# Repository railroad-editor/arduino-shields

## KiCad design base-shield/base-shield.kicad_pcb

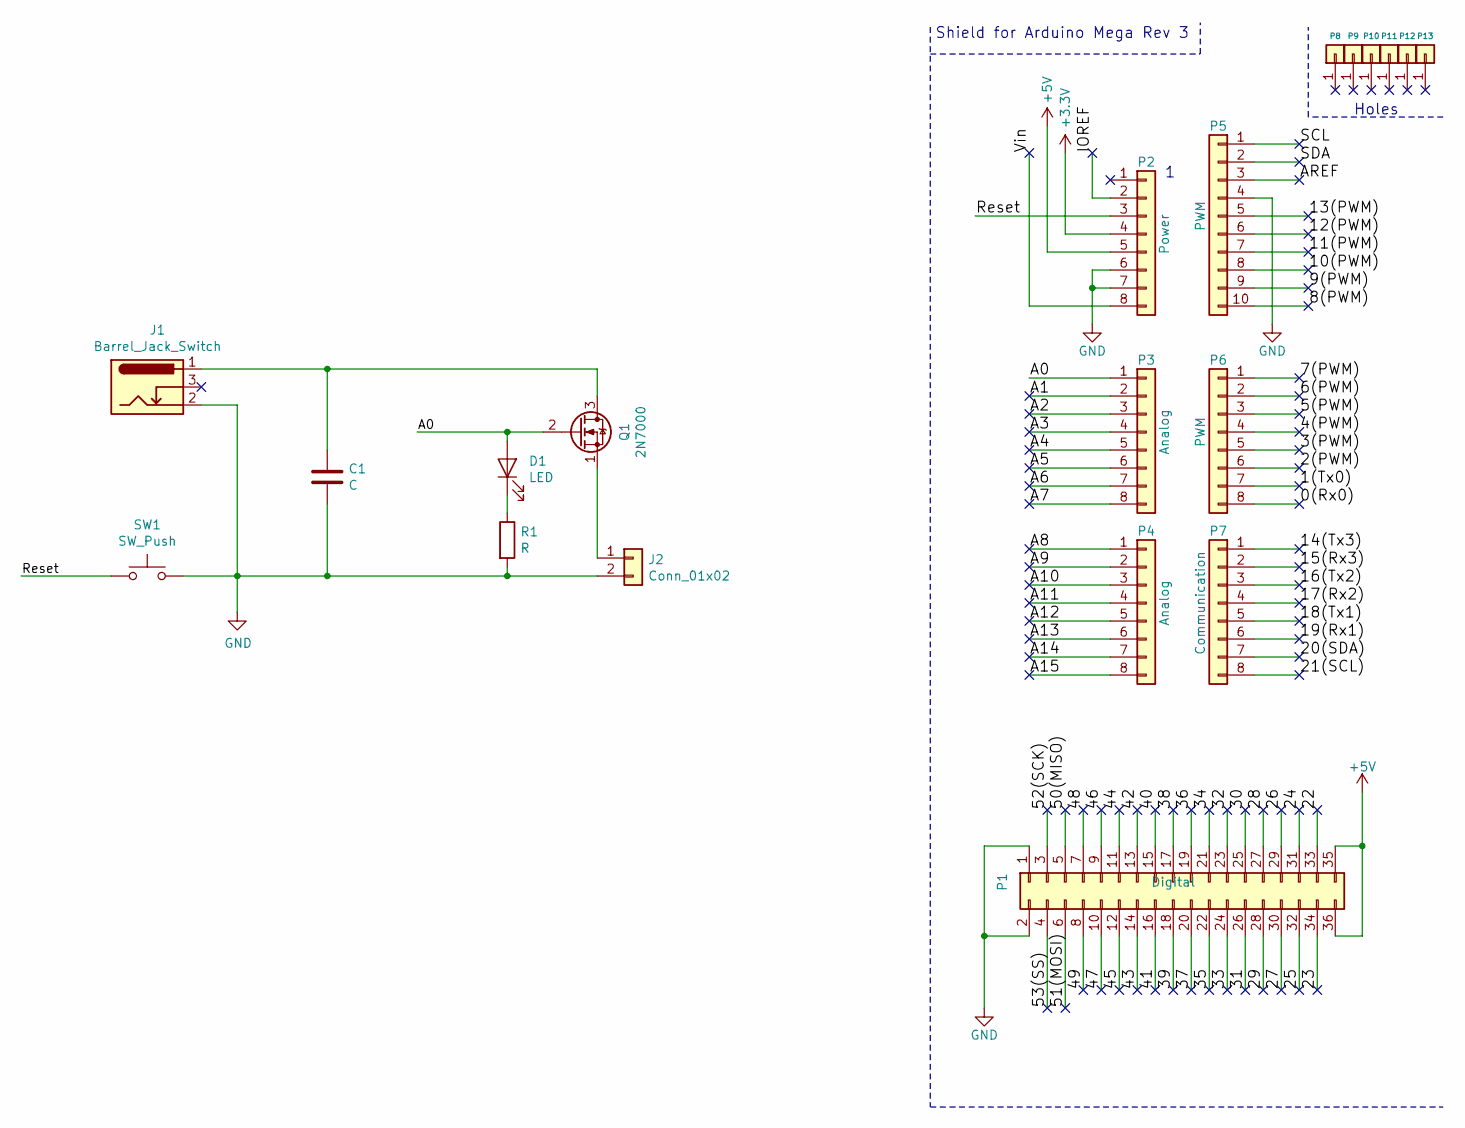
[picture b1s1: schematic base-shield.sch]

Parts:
C1: C; CP_Radial_D5.0mm_P2.50mm
D1: LED; LED_D3.0mm_Clear
J1: Barrel_Jack_Switch; BarrelJack_Horizontal
J2: Conn_01x02; PinSocket_1x02_P2.54mm_Vertical
P1: Digital; Socket_Strip_Arduino_2x18
P2: Power; Socket_Strip_Arduino_1x08
P3, P4: Analog; Socket_Strip_Arduino_1x08
P5: PWM; Socket_Strip_Arduino_1x10
P6: PWM; Socket_Strip_Arduino_1x08
P7: Communication; Socket_Strip_Arduino_1x08
P8, P9, P10, P11, P12, P13: CONN_01X01; Arduino_1pin
Q1: 2N7000; TO-126-3_Horizontal_TabDown
R1: R; R_Axial_DIN0204_L3.6mm_D1.6mm_P5.08mm_Horizontal
SW1: SW_Push; SW_PUSH_6mm

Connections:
+3V3: P2.4
+5V: P1.35, P1.36, P2.5
/0(Rx0): P6.8
/1(Tx0): P6.7
/2(PWM): P6.6
/3(PWM): P6.5
/4(PWM): P6.4
/5(PWM): P6.3
/6(PWM): P6.2
/7(PWM): P6.1
/8(PWM): P5.10
/9(PWM): P5.9
/10(PWM): P5.8
/11(PWM): P5.7
/12(PWM): P5.6
/13(PWM): P5.5
/14(Tx3): P7.1
/15(Rx3): P7.2
/16(Tx2): P7.3
/17(Rx2): P7.4
/18(Tx1): P7.5
/19(Rx1): P7.6
/20(SDA): P7.7
/21(SCL): P7.8
/22: P1.33
/23: P1.34
/24: P1.31
/25: P1.32
/26: P1.29
/27: P1.30
/28: P1.27
/29: P1.28
/30: P1.25
/31: P1.26
/32: P1.23
/33: P1.24
/34: P1.21
/35: P1.22
/36: P1.19
/37: P1.20
/38: P1.17
/39: P1.18
/40: P1.15
/41: P1.16
/42: P1.13
/43: P1.14
/44: P1.11
/45: P1.12
/46: P1.9
/47: P1.10
/48: P1.7
/49: P1.8
/50(MISO): P1.5
/51(MOSI): P1.6
/52(SCK): P1.3
/53(SS): P1.4
/A0: D1.2 (A), P3.1, Q1.2 (G)
/A1: P3.2
/A2: P3.3
/A3: P3.4
/A4: P3.5
/A5: P3.6
/A6: P3.7
/A7: P3.8
/A8: P4.1
/A9: P4.2
/A10: P4.3
/A11: P4.4
/A12: P4.5
/A13: P4.6
/A14: P4.7
/A15: P4.8
/AREF: P5.3
/IOREF: P2.2
/Reset: P2.3, SW1.1
/SCL: P5.1
/SDA: P5.2
/Vin: P2.8
GND: C1.2, J1.2, J2.2, P1.1, P1.2, P2.6, P2.7, P5.4, R1.2, SW1.2
unnamed: C1.1, J1.1, Q1.3 (D)
unnamed: D1.1 (K), R1.1
unnamed: J2.1, Q1.1 (S)

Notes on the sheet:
Shield for Arduino Mega Rev 3
Holes

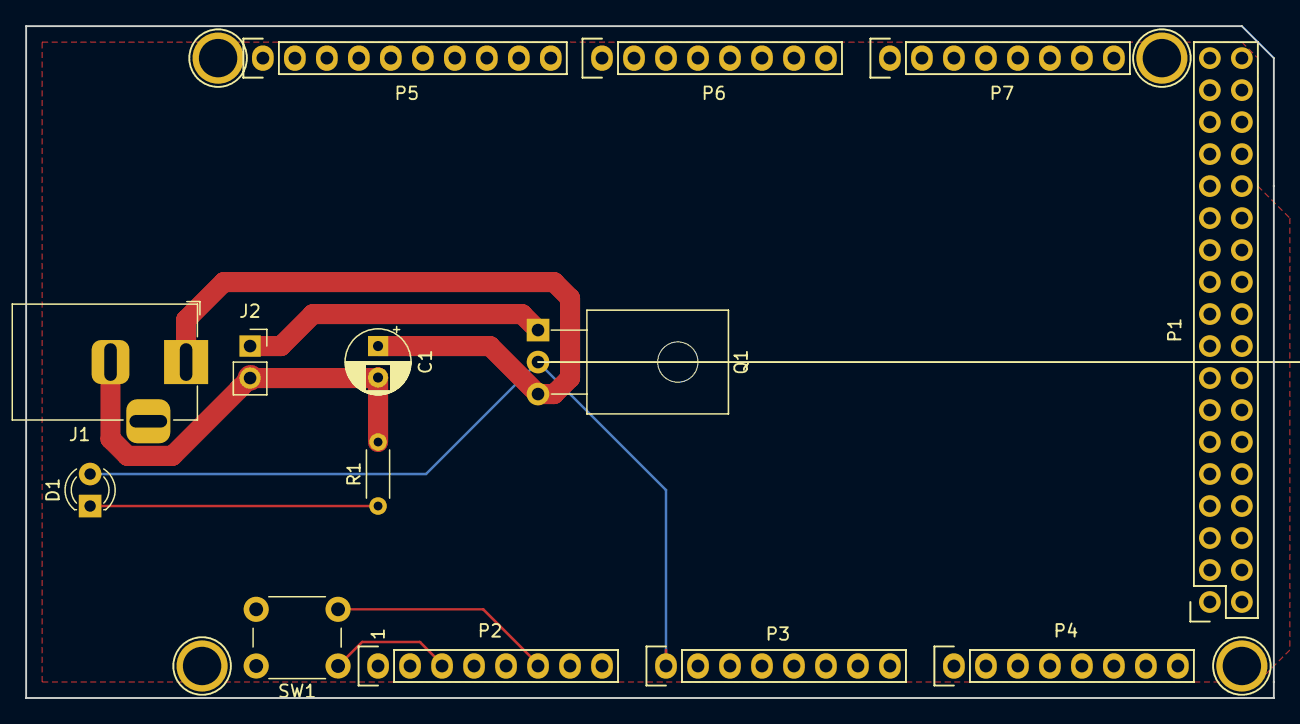
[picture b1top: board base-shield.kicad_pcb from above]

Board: 2 copper layers, 99.1 x 53.3 mm, 18 parts (0 on the bottom side), 7 nets.

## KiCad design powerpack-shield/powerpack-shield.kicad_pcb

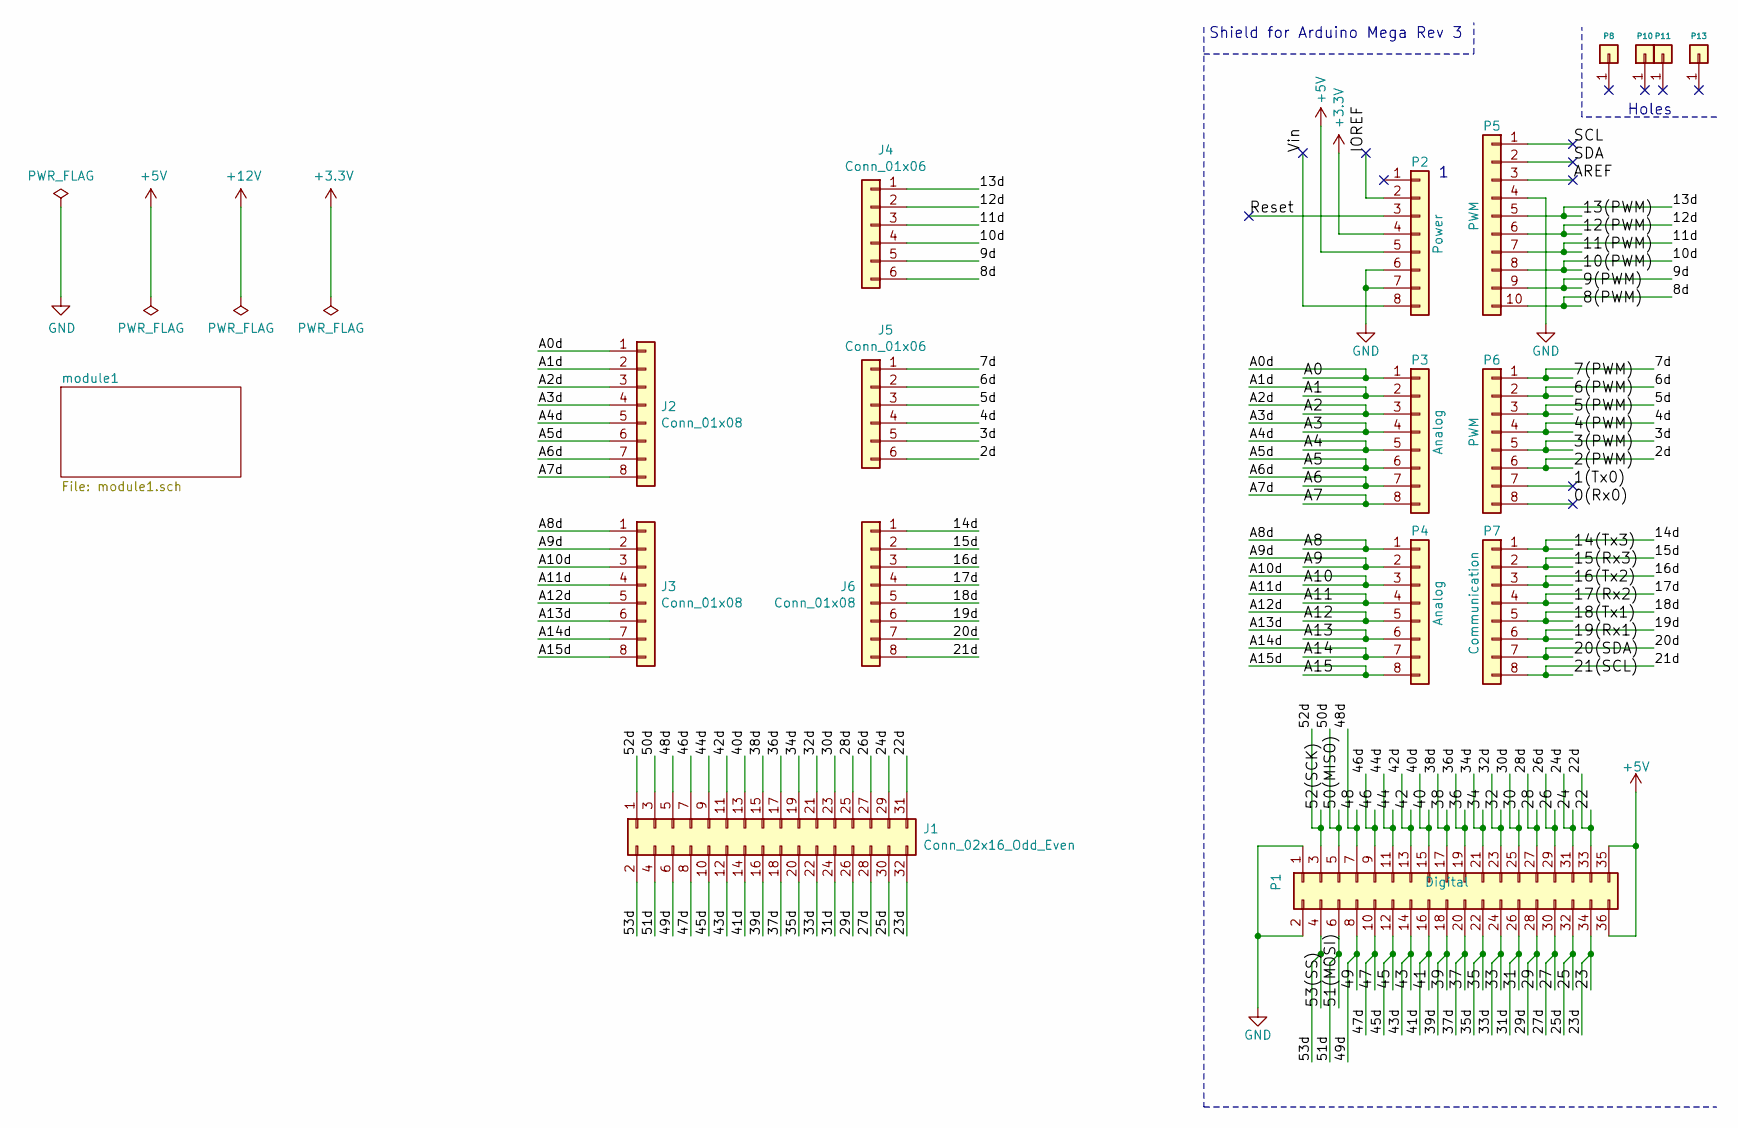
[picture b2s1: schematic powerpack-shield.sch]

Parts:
J1: Conn_02x16_Odd_Even; PinSocket_2x16_P2.54mm_Vertical
J2, J3, J6: Conn_01x08; PinSocket_1x08_P2.54mm_Vertical
J4, J5: Conn_01x06; PinSocket_1x06_P2.54mm_Vertical
P1: Digital; Socket_Strip_Arduino_2x18
P2: Power; Socket_Strip_Arduino_1x08
P3, P4: Analog; Socket_Strip_Arduino_1x08
P5: PWM; Socket_Strip_Arduino_1x10
P6: PWM; Socket_Strip_Arduino_1x08
P7: Communication; Socket_Strip_Arduino_1x08
P8, P10, P11, P13: CONN_01X01; Arduino_1pin

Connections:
+3V3: P2.4
+5V: P1.35, P1.36, P2.5; also elsewhere on the board
/0(Rx0): P6.8
/1(Tx0): P6.7
/2(PWM): J5.6, P6.6
/3(PWM): J5.5, P6.5
/4(PWM): J5.4, P6.4
/5(PWM): J5.3, P6.3
/6(PWM): J5.2, P6.2
/7(PWM): J5.1, P6.1
/8(PWM): J4.6, P5.10
/9(PWM): J4.5, P5.9
/10(PWM): J4.4, P5.8
/11(PWM): J4.3, P5.7
/12(PWM): J4.2, P5.6
/13(PWM): J4.1, P5.5
/14(Tx3): J6.1, P7.1
/15(Rx3): J6.2, P7.2
/16(Tx2): J6.3, P7.3
/17(Rx2): J6.4, P7.4
/18(Tx1): J6.5, P7.5
/19(Rx1): J6.6, P7.6
/20(SDA): J6.7, P7.7
/21(SCL): J6.8, P7.8
/22: J1.31, P1.33
/23: J1.32, P1.34
/24: J1.29, P1.31
/25: J1.30, P1.32
/26: J1.27, P1.29
/27: J1.28, P1.30
/28: J1.25, P1.27
/29: J1.26, P1.28
/30: J1.23, P1.25
/31: J1.24, P1.26
/32: J1.21, P1.23
/33: J1.22, P1.24
/34: J1.19, P1.21
/35: J1.20, P1.22
/36: J1.17, P1.19
/37: J1.18, P1.20
/38: J1.15, P1.17
/39: J1.16, P1.18
/40: J1.13, P1.15
/41: J1.14, P1.16
/42: J1.11, P1.13
/43: J1.12, P1.14
/44: J1.9, P1.11
/45: J1.10, P1.12
/46: J1.7, P1.9
/47: J1.8, P1.10
/48: J1.5, P1.7
/49: J1.6, P1.8
/50(MISO): J1.3, P1.5
/51(MOSI): J1.4, P1.6
/52(SCK): J1.1, P1.3
/53(SS): J1.2, P1.4
/A0: J2.1, P3.1
/A1: J2.2, P3.2
/A2: J2.3, P3.3
/A3: J2.4, P3.4
/A4: J2.5, P3.5
/A5: J2.6, P3.6
/A6: J2.7, P3.7
/A7: J2.8, P3.8
/A8: J3.1, P4.1
/A9: J3.2, P4.2
/A10: J3.3, P4.3
/A11: J3.4, P4.4
/A12: J3.5, P4.5
/A13: J3.6, P4.6
/A14: J3.7, P4.7
/A15: J3.8, P4.8
/AREF: P5.3
/IOREF: P2.2
/Reset: P2.3
/SCL: P5.1
/SDA: P5.2
/Vin: P2.8
GND: P1.1, P1.2, P2.6, P2.7, P5.4; also elsewhere on the board

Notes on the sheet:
Shield for Arduino Mega Rev 3
Holes

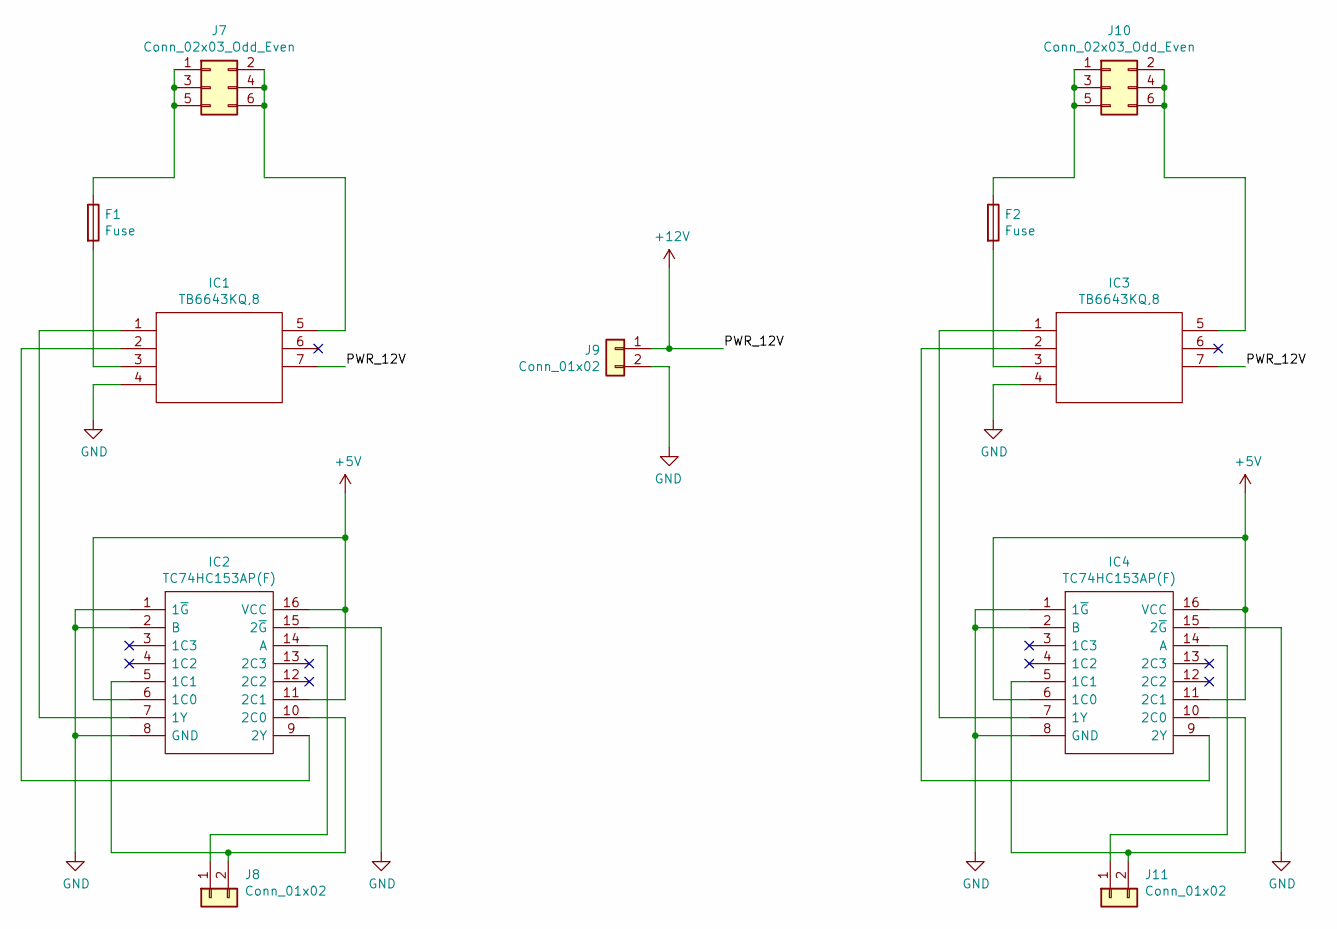
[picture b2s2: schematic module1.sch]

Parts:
F1, F2: Fuse; C_Disc_D7.5mm_W2.5mm_P5.00mm
IC1, IC3: TB6643KQ,8; HSIP7-P-2.54A; Manufacturer_Part_Number TB6643KQ,8; DigiKey Part Number TB6643KQ8-ND
IC2, IC4: TC74HC153AP(F); DIP762W60P254L1925H445Q16N; Manufacturer_Part_Number TC74HC153AP(F); Mouser Part Number N/A
J7, J10: Conn_02x03_Odd_Even; PinHeader_2x03_P2.54mm_Horizontal
J8, J9, J11: Conn_01x02; PinSocket_1x02_P2.54mm_Vertical

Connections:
+5V: IC2.6 (1C0), IC2.11 (2C1), IC2.16 (VCC), IC4.6 (1C0), IC4.11 (2C1), IC4.16 (VCC); also elsewhere on the board
+12V: IC1.7, IC3.7, J9.1
GND: IC1.4, IC2.1 (1~G), IC2.2 (B), IC2.8 (GND), IC2.15 (2~G), IC3.4, IC4.1 (1~G), IC4.2 (B), IC4.8 (GND), IC4.15 (2~G), J9.2; also elsewhere on the board
unnamed: F1.1, J7.1, J7.3, J7.5
unnamed: F1.2, IC1.3
unnamed: F2.1, J10.1, J10.3, J10.5
unnamed: F2.2, IC3.3
unnamed: IC1.1, IC2.7 (1Y)
unnamed: IC1.2, IC2.9 (2Y)
unnamed: IC1.5, J7.2, J7.4, J7.6
unnamed: IC2.5 (1C1), IC2.10 (2C0), J8.2
unnamed: IC2.14 (A), J8.1
unnamed: IC3.1, IC4.7 (1Y)
unnamed: IC3.2, IC4.9 (2Y)
unnamed: IC3.5, J10.2, J10.4, J10.6
unnamed: IC4.5 (1C1), IC4.10 (2C0), J11.2
unnamed: IC4.14 (A), J11.1

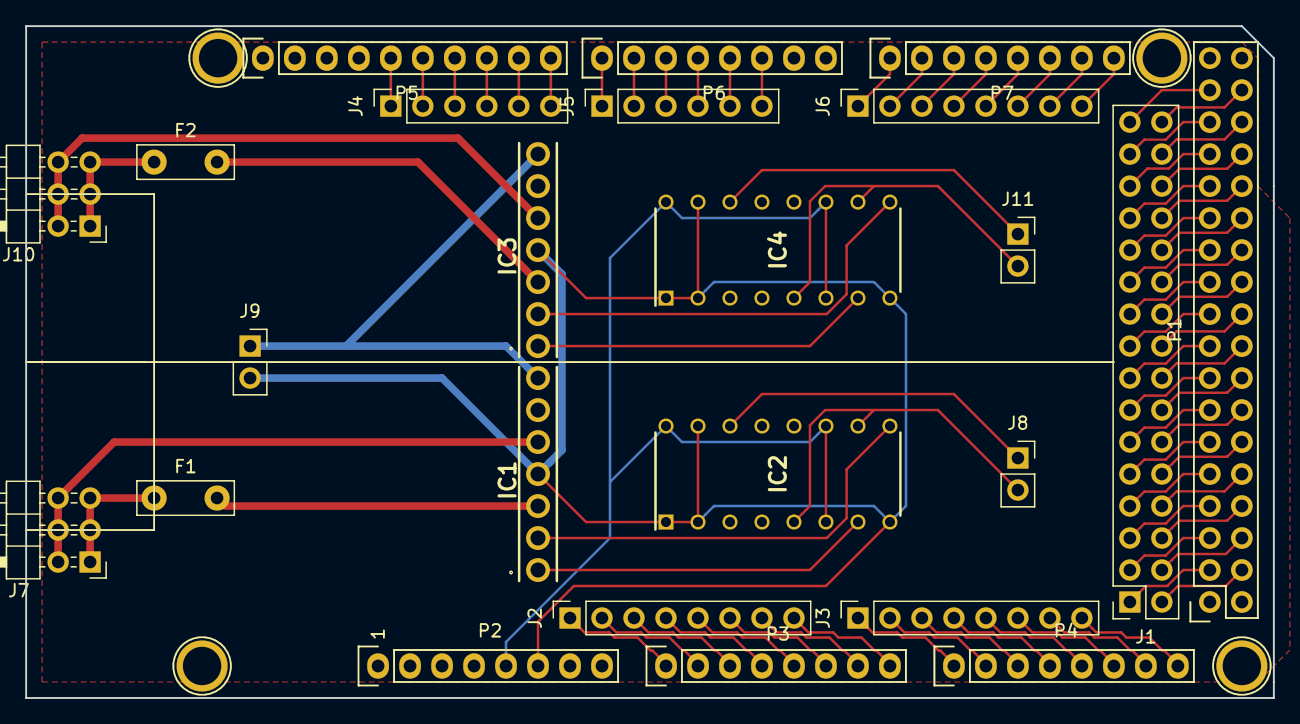
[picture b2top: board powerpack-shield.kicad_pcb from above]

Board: 2 copper layers, 99.1 x 53.3 mm, 28 parts (0 on the bottom side), 85 nets.
